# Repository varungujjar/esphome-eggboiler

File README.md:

# ESP Home based Egg Cooker

Smart Egg Cooker – Automate Your Breakfast Routine!

Upgrade your mornings with this intelligent Egg Cooker, designed to automate and perfect your breakfast routine. Equipped with a DS18B20 temperature sensor, it precisely monitors the boiling water, ensuring your eggs are cooked to perfection. A Piezo Buzzer alerts you when the cooker connects to WiFi and when your eggs are ready.

Seamlessly integrate it with Home Assistant for a smart home experience. Plus, with access to schematics and PCB Gerber files, you can fully customize and enhance its features to suit your needs.

Enjoy hassle-free, perfectly cooked eggs—every time!

## Features  

- Automate your morning breakfast routines with this egg cooker
- Temperature sensor using DS18B20 keeps track of the boiling water
- Piezo Buzzer plays sound when connected to Wifi & when egg is cooked
- Compatible with **Home Assistant** for seamless integration.  
- Access to schematics and PCB Gerber files.  
- Fully customizable for advanced features.  

## Requirements  

- **Home Assistant** (Standalone software version coming soon).  
- **USB-to-Serial Hardware** to program the ESP8266 12E.  
- **ESPHome Setup Guide**: [Getting Started with ESPHome](https://esphome.io/guides/getting_started_hassio.html).  

## Demo  
[Full Video](https://youtu.be/4700ta0FNh4).  

Follow us for more exciting projects and updates:  

## License  

This project is licensed under the **GPL-3.0 License**. [Learn More](https://www.gnu.org/licenses/gpl-3.0).

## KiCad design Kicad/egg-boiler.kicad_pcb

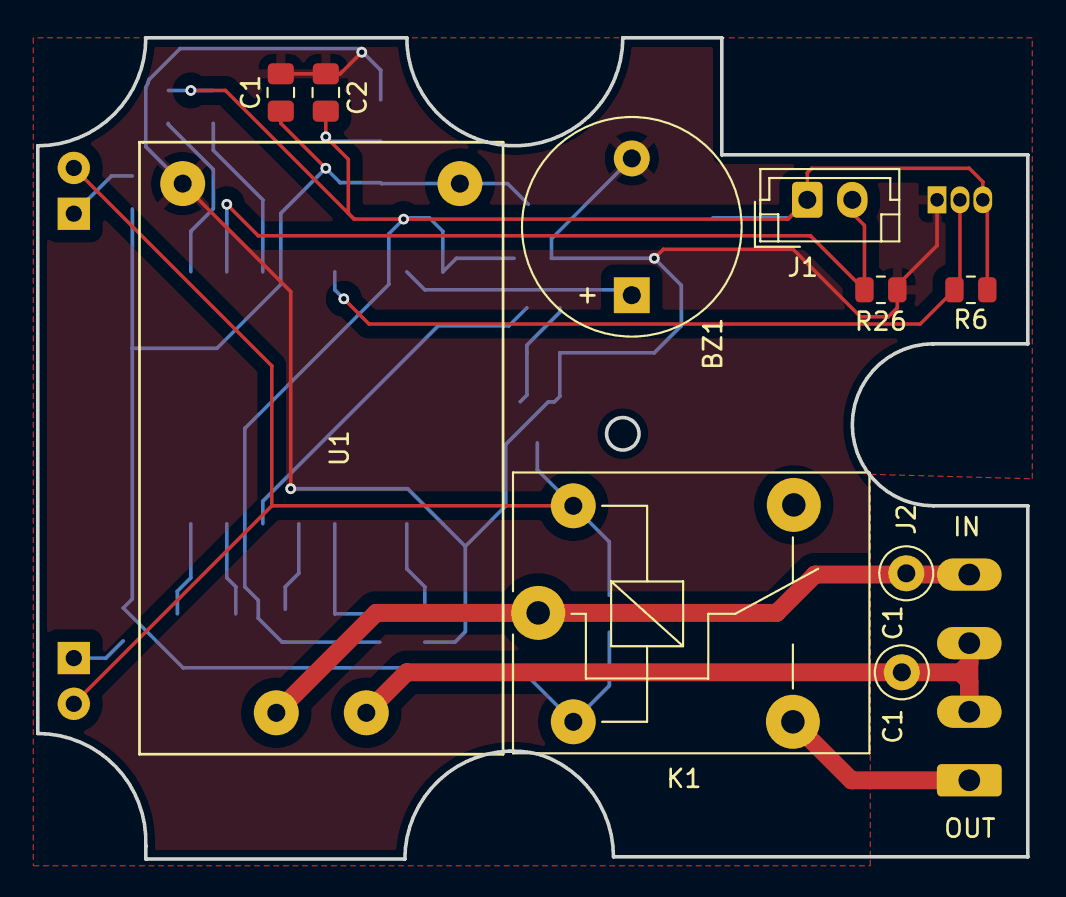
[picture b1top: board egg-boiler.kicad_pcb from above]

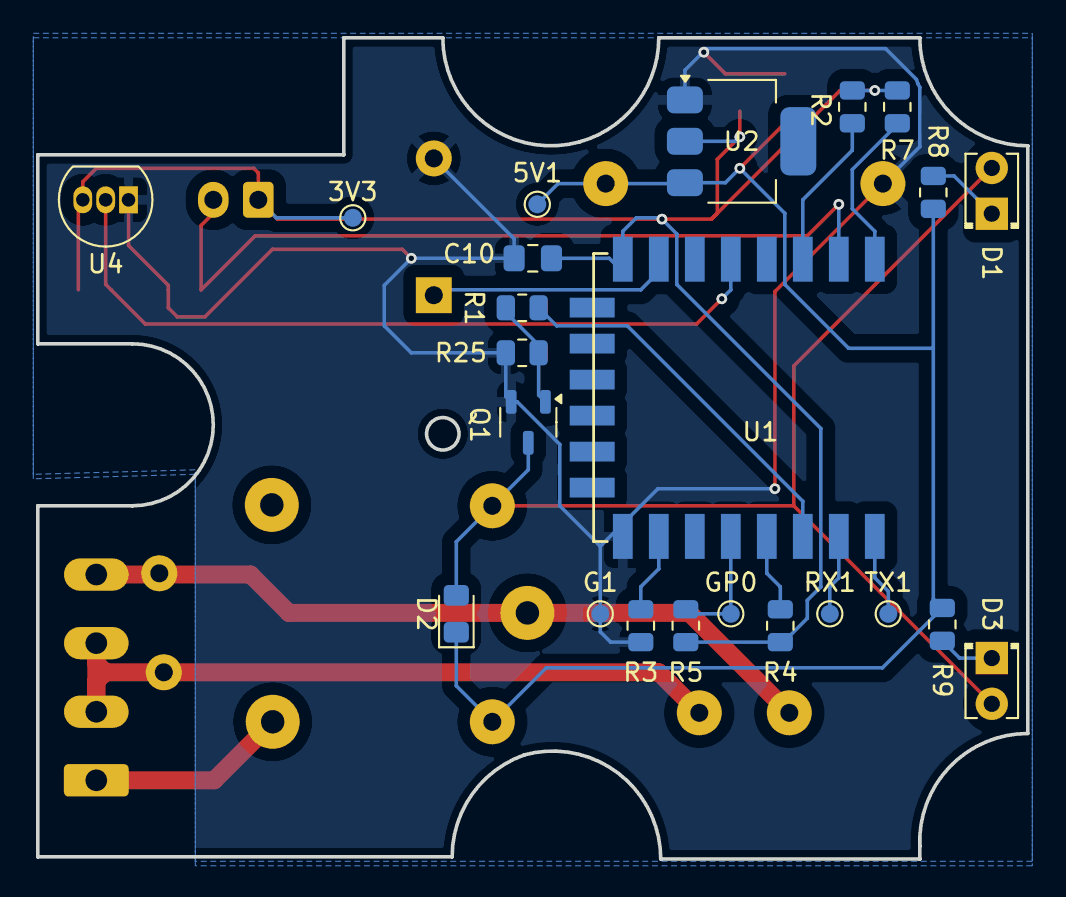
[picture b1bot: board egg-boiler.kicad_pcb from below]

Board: 2 copper layers, 55.0 x 45.6 mm, 34 parts (23 on the bottom side), 21 nets.

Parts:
3V3, 5V1: Conn_01x01; TestPoint_Pad_D1.0mm
BZ1: Buzzer; Buzzer_12x9.5RM7.6
C1, C1#2: C0; TestPoint_Loop_D1.80mm_Drill1.0mm_Beaded
C1#3, C2, C10: 100nf; C_0805_2012Metric_Pad1.18x1.45mm_HandSolder
D1, D3: LED; LED_D2.0mm_W4.0mm_H2.8mm_FlatTop
D2: IN4148; D_0805_2012Metric_Pad1.15x1.40mm_HandSolder
G1: Conn_01x01; TestPoint_Pad_D1.0mm
GP0: Conn_01x01; TestPoint_Pad_D1.0mm
J1: Thermistor; JST_EH_B2B-EH-A_1x02_P2.50mm_Vertical
J2: MAINS; PhoenixContact_MCV_1,5_4-G-3.81_1x04_P3.81mm_Vertical_Custom
K1: Relay; Relay_SPDT_SANYOU_SRD_Series_Form_C
Q1: 2N7002; SOT-23-3
R1: 1K; R_0805_2012Metric
R2, R3, R4, R5, R7, R25, R26: 10K; R_0805_2012Metric
R6: 4.7K; R_0805_2012Metric
R8, R9: 300; R_0805_2012Metric
RX1: Conn_01x01; TestPoint_Pad_D1.0mm
TX1: Conn_01x01; TestPoint_Pad_D1.0mm
U1: HLK-PM03; HLK-PM01
U1#2: ESP-12E; ESP-12E_SMD
U2: AP1117; SOT-223
U4: DS18B20; TO-92_Inline

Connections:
3V3: 3V3.1, C2.1, C10.1, J1.1, R2.1, R4.1, R5.1, R6.1, R7.1, U1#2.8 (VCC), U2.2 (VO), U4.3 (V_{DD})
5V: 5V1.1, C1#3.1, D2.1 (K), K1.2, R8.1, R9.1, U1.4 (DC+), U2.3 (VI)
ADC: J1.2, R26.1, U1#2.2 (ADC)
GND: BZ1.2 (-), C1#3.2, C2.2, C10.2, G1.1, Q1.2 (E), R3.2, R25.1, R26.2, U1.3 (DC-), U1#2.9 (GND), U2.1 (GND/ADJ), U4.1 (GND)
GPIO0: GP0.1, R5.2, U1#2.12 (GPIO0)
GPIO5: R1.2, U1#2.14 (GPIO5)
GPIO13: BZ1.1 (+), U1#2.7 (GPIO13)
GPIO14: R6.2, U1#2.5 (GPIO14), U4.2 (DQ)
LED: D1.2 (A), D2.2 (A), D3.2 (A), K1.5, Q1.3 (C)
unnamed: D1.1 (K), R8.2
unnamed: D3.1 (K), R9.2
unnamed: J2.1, K1.3
unnamed: J2.2, J2.3, U1.2 (L2)
unnamed: J2.4, K1.1, U1.1 (L1)
unnamed: Q1.1 (B), R1.1, R25.2
unnamed: R2.2, U1#2.3 (CH_PD)
unnamed: R4.2, U1#2.13 (GPIO4)
unnamed: R3.1, U1#2.10 (GPIO15)
unnamed: R7.2, U1#2.1 (REST)
RXD: RX1.1, U1#2.15 (RXD)
TXD: TX1.1, U1#2.16 (TXD)

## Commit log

2025-03-26 Initialise Files
    ESP Home yaml, PCB & Schematics

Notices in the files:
README.md:
License: GPL-3.0
